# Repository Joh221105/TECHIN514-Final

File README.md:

# Bloop
An interactive desk companion featuring a magnetically-controlled ferrofluid that responds to hand gestures (and potentially audio commands in the future). The creature exhibits lifelike behaviors through computer vision and wireless control. Core Behaviors:

Follow - Tracks and follows user's face position
Hide - Rotates away from user (shy behavior)
Spin - Runs around the track once

### Physical Features
A circular acrylic platform (12" diameter) contains ferrofluid in carved tracks. Beneath the platform, a stepper motor controls an arm with an embedded magnet rotates to manipulate the fluid. An LED ring provides ambient lighting and behavioral feedback.

# Sensor Device

### ESP32-C3
The sensing device uses an ESP32C3 with a SEN0359-EN voice recognition module to detect command words and move the stepper motor accordingly to make the ferrofluid perform the "tricks".

The device is powered by a 150mAh 3.7V LiPo battery with USB charging, making it portable and easily repositionable. 

# Display Device

### Magnetically-Actuated Ferrofluid Platform
The display device features a laser-cut circular acrylic platform with ferrofluid in carved tracks. A NEMA 17 stepper motor beneath the platform rotates a vertical arm assembly, positioning a neodymium magnet 1-2mm under the ferrofluid. The TMC2208 driver provides silent operation with microstepping for smooth, organic motion.

An ESP32-C3 microcontroller receives wireless commands and controls motor movements. A WS2812B LED ring (16 LEDs) provides visual feedback with color-coded patterns. A capacitive touch pad enables power control, and an 11.1V 2200mAh LiPo battery provides power and allows portability.

As the magnet rotates, the ferrofluid forms dramatic spikes that follow the magnetic field, creating lifelike tracking behaviors that respond to user movements detected by the camera.

# Communication Between Devices

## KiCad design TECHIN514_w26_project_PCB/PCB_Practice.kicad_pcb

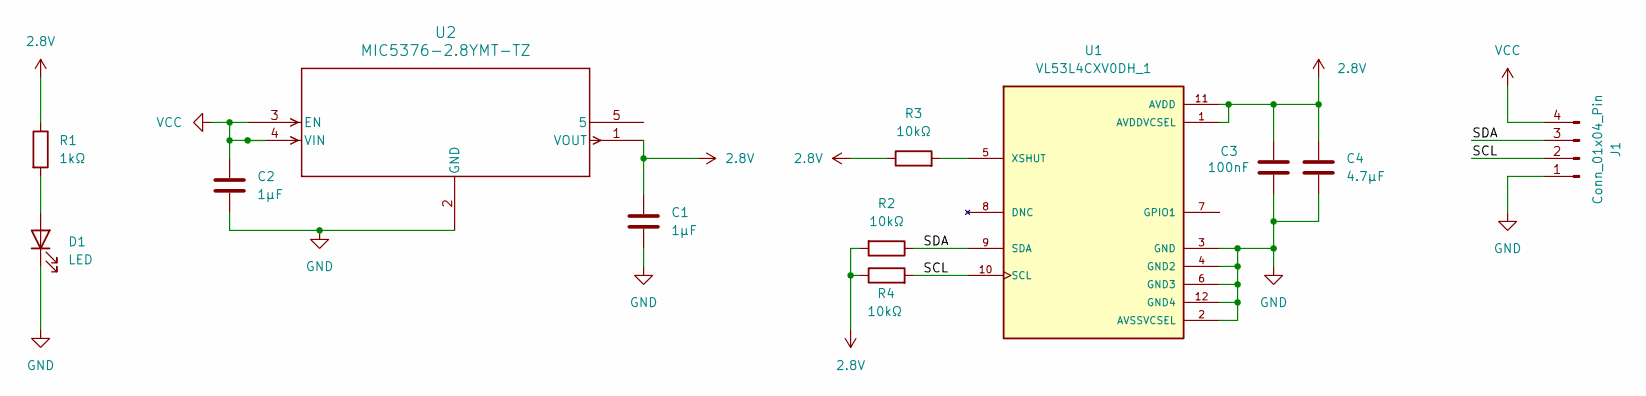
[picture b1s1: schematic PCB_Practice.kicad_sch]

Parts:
C1, C2: 1µF; C_0402_1005Metric_Pad0.74x0.62mm_HandSolder
C3: 100nF; C_0402_1005Metric_Pad0.74x0.62mm_HandSolder
C4: 4.7µF; C_0402_1005Metric_Pad0.74x0.62mm_HandSolder
D1: LED; LED_0402_1005Metric_Pad0.77x0.64mm_HandSolder
J1: Conn_01x04_Pin; PinSocket_1x04_P2.54mm_Vertical
R1: 1kΩ; R_0402_1005Metric_Pad0.72x0.64mm_HandSolder
R2, R3, R4: 10kΩ; R_0402_1005Metric_Pad0.72x0.64mm_HandSolder
U1: VL53L4CXV0DH_1; XCDR_VL53L4CXV0DH_1; PARTREV 4
U2: MIC5376-2.8YMT-TZ; SC-70_C5_MCH-L

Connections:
2.8V: C1.1, C3.1, C4.2, R1.1, R2.2, R3.1, R4.1, U1.1 (AVDDVCSEL), U1.11 (AVDD), U2.1 (VOUT)
/SCL: J1.2, R4.2, U1.10 (SCL)
/SDA: J1.3, R2.1, U1.9 (SDA)
GND: C1.2, C2.2, C3.2, C4.1, D1.1 (K), J1.1, U1.2 (AVSSVCSEL), U1.3 (GND), U1.4 (GND2), U1.6 (GND3), U1.12 (GND4), U2.2 (GND)
unnamed: D1.2 (A), R1.2
unnamed: R3.2, U1.5 (XSHUT)
VCC: C2.1, J1.4, U2.3 (EN), U2.4 (VIN)

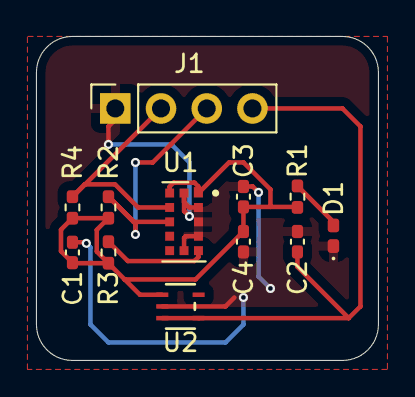
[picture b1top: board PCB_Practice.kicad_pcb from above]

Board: 2 copper layers, 19.0 x 18.0 mm, 12 parts (0 on the bottom side), 7 nets.

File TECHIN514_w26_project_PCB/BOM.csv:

"#","Reference","Qty","Value","Footprint","DNP"
"1","C1, C2","2","1µF","Capacitor_SMD:C_0402_1005Metric_Pad0.74x0.62mm_HandSolder",""
"2","C3","1","100nF","Capacitor_SMD:C_0402_1005Metric_Pad0.74x0.62mm_HandSolder",""
"3","C4","1","4.7µF","Capacitor_SMD:C_0402_1005Metric_Pad0.74x0.62mm_HandSolder",""
"4","D1","1","LED","LED_SMD:LED_0402_1005Metric_Pad0.77x0.64mm_HandSolder",""
"5","J1","1","Conn_01x04_Pin","Connector_PinSocket_2.54mm:PinSocket_1x04_P2.54mm_Vertical",""
"6","R1","1","1kΩ","Resistor_SMD:R_0402_1005Metric_Pad0.72x0.64mm_HandSolder",""
"7","R2, R3, R4","3","10kΩ","Resistor_SMD:R_0402_1005Metric_Pad0.72x0.64mm_HandSolder",""
"8","U1","1","VL53L4CXV0DH_1","L3KicadFoot:XCDR_VL53L4CXV0DH_1",""
"9","U2","1","MIC5376-2.8YMT-TZ","L3KicadFoot:SC-70_C5_MCH-L",""

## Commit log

2026-01-20 add sketches and diagrams to assets, add component datasheet pdfs to datasheets
2026-01-20 Update title in readme
2026-01-27 update architectural system and add electrical diagram
2026-01-29 add kicad files for pcb design lab 3
2026-01-30 add ground plane to back of pcb
2026-02-08 add Battery Life Estimate assignment
2026-03-02 add src folder with current sensor and display code
2026-03-02 add .gitignore file
2026-03-16 add updated display and sensor code
